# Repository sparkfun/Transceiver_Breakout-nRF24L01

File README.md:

SparkFun Transceiver Breakout - nRF24L01+
========================================

[*SparkFun Transceiver Breakout - nRF24L01+ (WRL-00691)*](https://www.sparkfun.com/products/691)

This module uses the newest 2.4GHz transceiver from Nordic Semiconductor, the nRF24L01+. 
This transceiver IC operates in the 2.4GHz band and has many new features! 
Take all the coolness of the nRF2401A and add some extra pipelines, buffers, and an auto-retransmit feature - very nice!

Repository Contents
-------------------

* **/Hardware** - Eagle design files (.brd, .sch)
* **/Libraries** - Libraries for use with the 
* **/Production** - Production panel files (.brd)
* **/Software** - Related software for the <PRODUCT NAME>

Documentation
--------------
* **[Hookup Guide](https://learn.sparkfun.com/tutorials/nrf24l01-transceiver-hookup-guide)** - Basic hookup guide.
* **[SparkFun Fritzing repo](https://github.com/sparkfun/Fritzing_Parts)** - Fritzing diagrams for SparkFun products.
* **[SparkFun 3D Model repo](https://github.com/sparkfun/3D_Models)** - 3D models of SparkFun products. 

License Information
-------------------
This product is _**open source**_! 

The **hardware** is released under [Creative Commons ShareAlike 4.0 International](https://creativecommons.org/licenses/by-sa/4.0/).

The **code** is beerware; if you see me (or any other SparkFun employee) at the local, and you've found our code helpful, please buy us a round!

Please use, reuse, and modify these files as you see fit. Please maintain attribution to SparkFun Electronics and release anything derivative under the same license.

Distributed as-is; no warranty is given.

- Your friends at SparkFun.

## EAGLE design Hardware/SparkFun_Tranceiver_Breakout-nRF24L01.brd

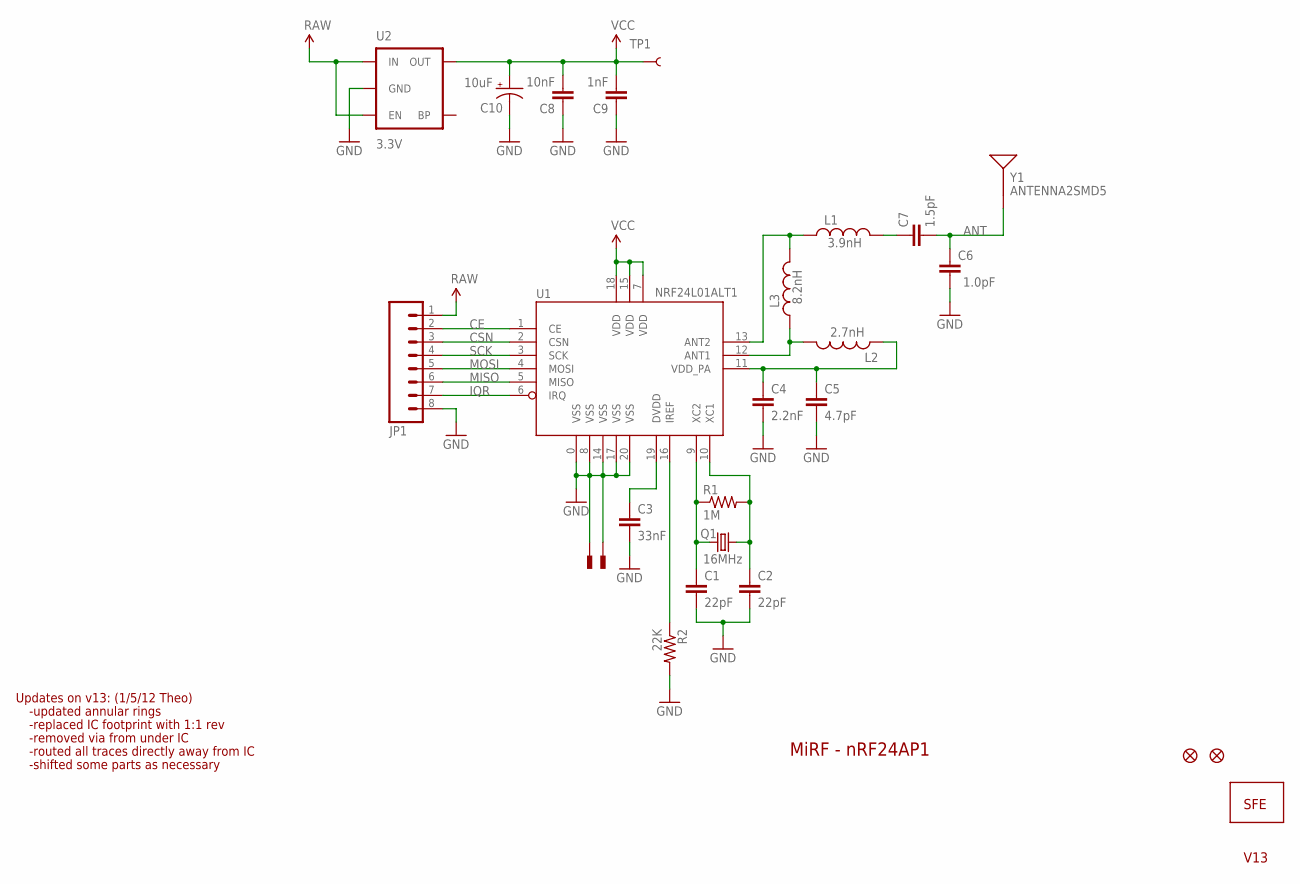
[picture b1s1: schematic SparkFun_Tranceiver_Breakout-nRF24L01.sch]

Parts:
C1, C2: 22pF; 0402-CAP
C3: 33nF; 0402-CAP
C4: 2.2nF; 0402-CAP
C5: 4.7pF; 0402-CAP
C6: 1.0pF; 0402-CAP
C7: 1.5pF; 0402-CAP
C8: 10nF; 0402-CAP
C9: 1nF; 0402-CAP
C10: 10uF; EIA3216
JP1: M081X08; 1X08
JP2, JP3: FIDUCIALUFIDUCIAL; MICRO-FIDUCIAL
L1: 3.9nH; C0402
L2: 2.7nH; C0402
L3: 8.2nH; C0402
Q1: 16MHz; CRYSTAL-SMD-5X3
R1: 1M; 0402-RES
R2: 22K; 0402-RES
TP1: TEST-POINT3X5; PAD.03X.05
U1: NRF24L01ALT1; QFN20_ALT1
U2: 3.3V; SOT23-5
U$1, U$4: PAD; PAD-0.008
U$5: LOGO-SFENEW; SFE-NEW-WEBLOGO
Y1: ANTENNA2SMD5; ANTENNA-CHIP5

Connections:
ANT: C6.2, C7.2, Y1.FEED
CE: JP1.2, U1.1 (CE)
CSN: JP1.3, U1.2 (CSN)
GND: C1.2, C2.2, C3.2, C4.2, C5.2, C6.1, C8.1, C9.1, C10.C (-), JP1.8, R2.2, U1.0 (VSS), U1.8 (VSS), U1.14 (VSS), U1.17 (VSS), U1.20 (VSS), U2.2 (GND), U$1.P$1, U$4.P$1
IQR: JP1.7, U1.6 (IRQ)
MISO: JP1.6, U1.5 (MISO)
MOSI: JP1.5, U1.4 (MOSI)
unnamed: C1.1, Q1.1, R1.1, U1.9 (XC2)
unnamed: C2.1, Q1.3 (2), R1.2, U1.10 (XC1)
unnamed: L2.2, L3.1, U1.12 (ANT1)
unnamed: R2.1, U1.16 (IREF)
unnamed: C3.1, U1.19 (DVDD)
unnamed: L1.1, L3.2, U1.13 (ANT2)
unnamed: C4.1, C5.1, L2.1, U1.11 (VDD_PA)
unnamed: C7.1, L1.2
RAW: JP1.1, U2.1 (IN), U2.3 (EN)
SCK: JP1.4, U1.3 (SCK)
VCC: C8.2, C9.2, C10.A (+), TP1.P$1, U1.7 (VDD), U1.15 (VDD), U1.18 (VDD), U2.5 (OUT)

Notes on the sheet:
MiRF - nRF24AP1
Updates on v13: (1/5/12 Theo)
-updated annular rings
-replaced IC footprint with 1:1 rev
-removed via from under IC
-routed all traces directly away from IC
-shifted some parts as necessary
V13

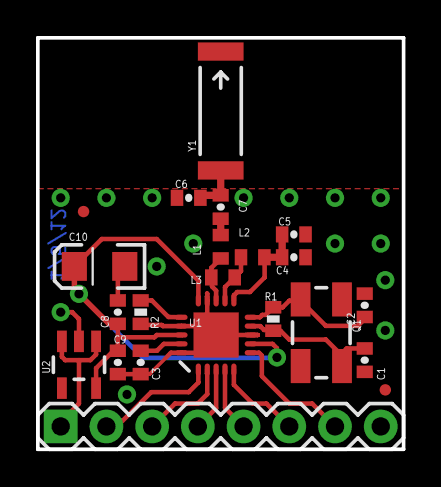
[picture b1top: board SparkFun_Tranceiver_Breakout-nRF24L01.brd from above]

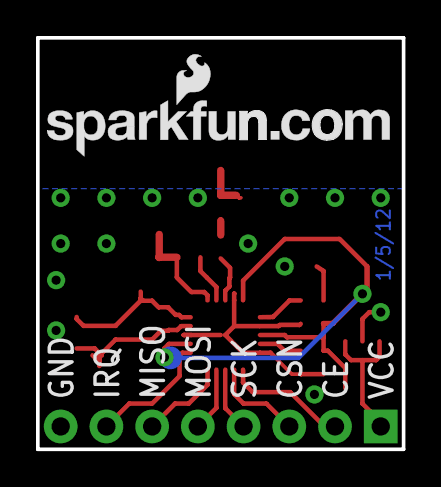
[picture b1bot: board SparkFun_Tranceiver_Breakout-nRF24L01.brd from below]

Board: 2 copper layers, 20.3 x 22.9 mm, 26 parts (2 on the bottom side), 18 nets.

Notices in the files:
parts and their libraries:
SparkFun-Aesthetics: Licensing: CC v3.0 Share-Alike You are welcome to use this library for commercial purposes.
SparkFun-Retired: Licensing:Creative Commons ShareAlike 4.0 International - https://creativecommons.org/licenses/by-sa/4.0
